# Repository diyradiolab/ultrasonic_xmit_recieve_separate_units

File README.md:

# ultrasonic_xmit_recieve_separate_units
ultrasonic transmitter and receiver units. transmitter is at 40khz on and off. receiver has several output frequencies and on off. single button control of states to cycle between them

This is for radio class

.INO files are arduino files. Code is mostly AVR-GCC C code.

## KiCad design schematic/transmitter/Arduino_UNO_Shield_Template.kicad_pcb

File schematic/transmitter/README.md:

Kicad circuit
Made in kicad v4.07
12-31-2017

The PDF in this file contains an image of the schematic: https://github.com/diyradiolab/ultrasonic_xmit_recieve_separate_units/blob/master/schematic/transmitter/Arduino_UNO_Shield_Template.pdf

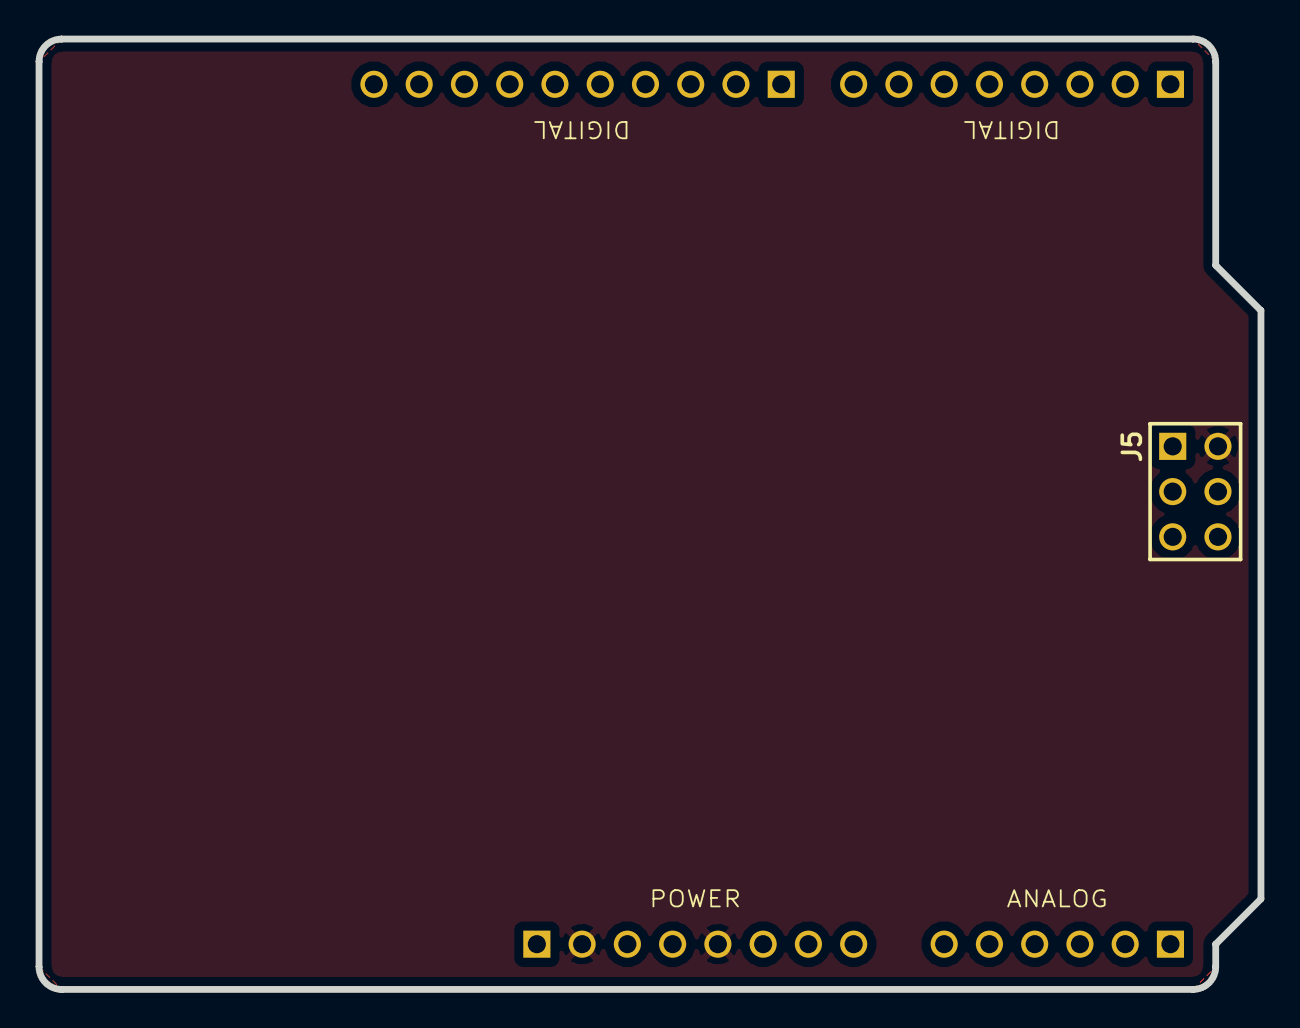
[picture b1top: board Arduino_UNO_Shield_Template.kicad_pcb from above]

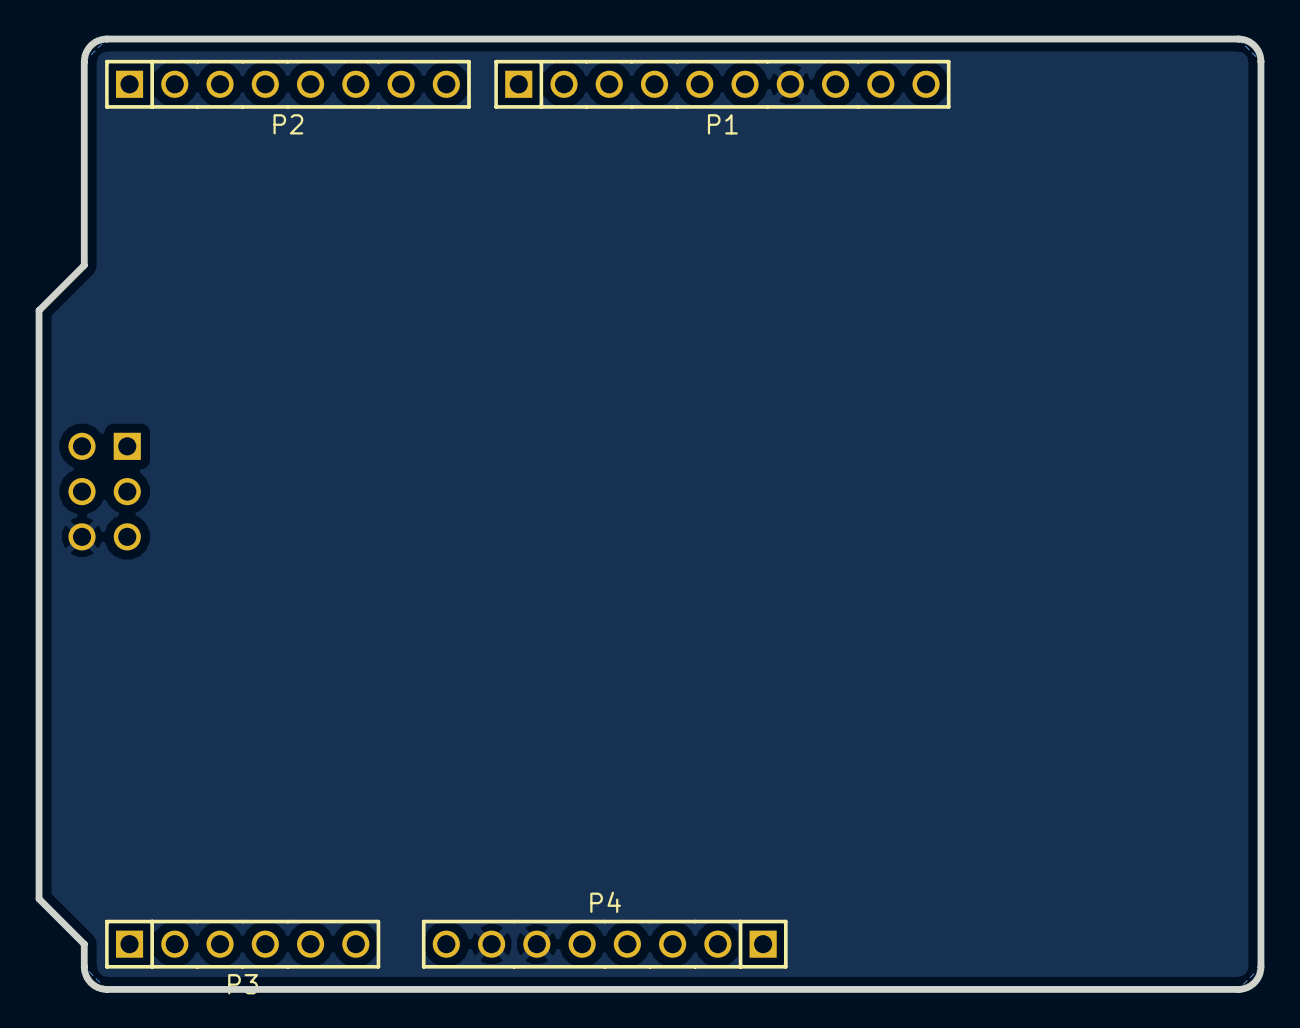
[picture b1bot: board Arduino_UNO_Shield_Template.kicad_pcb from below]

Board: 2 copper layers, 68.6 x 53.3 mm, 5 parts (4 on the bottom side), 8 nets, no tracks yet.

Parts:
J5: HEADER_F_2.54MM_2R6P_ST_AU_PTH; HEADER_F_100MIL_2R6P_ST_GOLD_PTH
P1: HEADER_M_2.54MM_1R10P_ST_AU_PTH
P2, P4: HEADER_M_2.54MM_1R8P_ST_AU_PTH
P3: HEADER_M_2.54MM_1R6P_ST_AU_PTH

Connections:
5V: J5.2, P4.2, P4.5
AD4/SDA: P1.9, P3.5
AD5/SCL: P1.10, P3.6
GND: J5.6, P1.7, P4.6, P4.7
IO11/MOSI: J5.4, P1.4
IO12/MISO: J5.1, P1.5
IO13/SCK: J5.3, P1.6
RESET: J5.5, P4.3
